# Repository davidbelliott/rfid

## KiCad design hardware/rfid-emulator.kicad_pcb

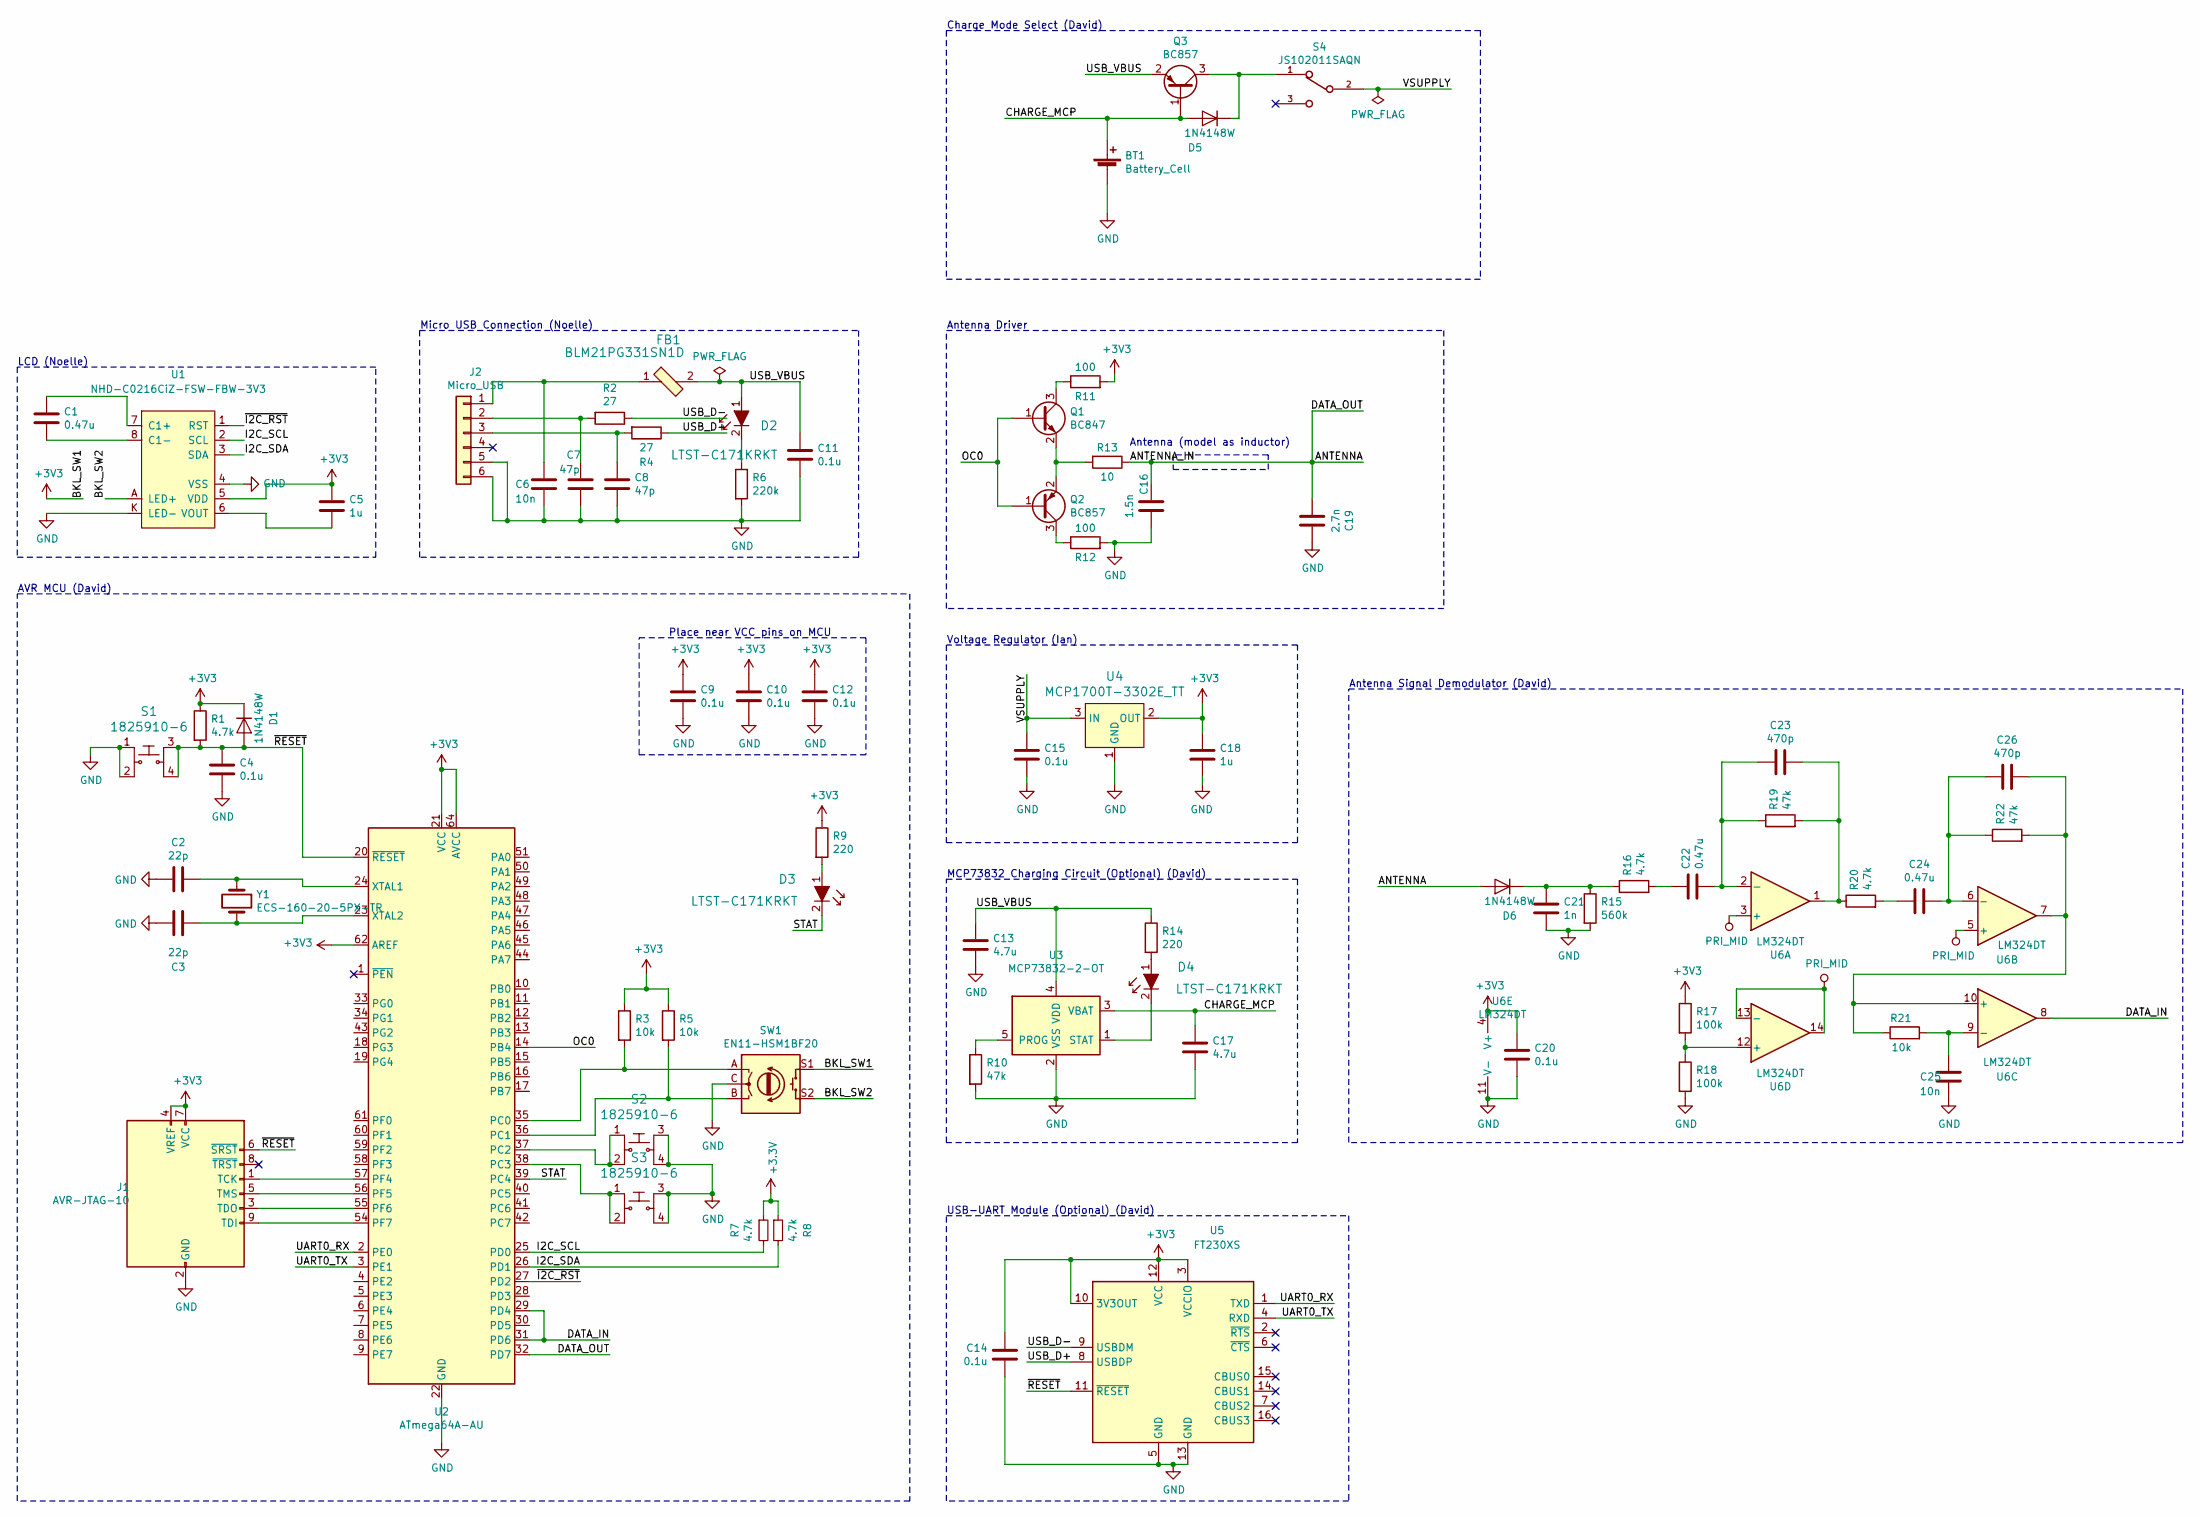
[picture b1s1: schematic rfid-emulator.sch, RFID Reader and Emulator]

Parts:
BT1: Battery_Cell; KEYSTONE-3034; Part RJD2032C1
C1: 0.47u; C_0805_HandSoldering; Part C0805C474K5RECTU
C2, C3: 22p; C_0805_HandSoldering
C4, C9, C10, C11, C12, C14, C15, C20: 0.1u; C_0805_HandSoldering; Part C0805C104Z5VACTU
C5, C18: 1u; C_0805_HandSoldering; Part CC0805ZRY5V8BB105
C6, C25: 10n; C_0805_HandSoldering; Part C0805C103K1RAC7210
C7, C8: 47p; C_0805_HandSoldering; Part C0805C470J5GACTU
C13, C17: 4.7u; C_0805_HandSoldering; Part CC0805ZRY5V6BB475
C16: 1.5n; C_0805_HandSoldering
C19: 2.7n; C_0805_HandSoldering
C21: 1n; C_0805_HandSoldering
C22, C24: 0.47u; C_0805_HandSoldering
C23, C26: 470p; C_0805_HandSoldering
D1, D5, D6: 1N4148W; D_SOD-123
D2, D3, D4: LTST-C171KRKT; 0805; MPN LTST-C171KRKT; Digi-Key_PN 160-1427-1-ND
FB1: BLM21PG331SN1D; 0805; MPN BLM21PG331SN1D; Digi-Key_PN 490-5988-1-ND
J1: AVR-JTAG-10; jtag-header; Part 302-S101
J2: Micro_USB; USB_Micro-B_Molex_47346-0001; Part Molex 47346-0001
Q1: BC847; SOT-23
Q2, Q3: BC857; SOT-23
R1, R7, R8, R16, R20: 4.7k; R_0805_HandSoldering
R2, R4: 27; R_0805_HandSoldering
R3, R5, R21: 10k; R_0805_HandSoldering
R6: 220k; R_0805_HandSoldering
R9, R14: 220; R_0805_HandSoldering
R10, R19, R22: 47k; R_0805_HandSoldering
R11, R12: 100; R_0805_HandSoldering
R13: 10; R_0805_HandSoldering
R15: 560k; R_0805_HandSoldering
R17, R18: 100k; R_0805_HandSoldering
S1, S2, S3: 1825910-6; Switch_Tactile_THT_6x6mm; MPN 1825910-6; Digi-Key_PN 450-1650-ND
S4: JS102011SAQN; SW_JS102011SAQN
SW1: EN11-HSM1BF20
U1: NHD-C0216CiZ-FSW-FBW-3V3; NHD-C0216CiZ
U2: ATmega64A-AU; TQFP-64_14x14mm_Pitch0.8mm
U3: MCP73832-2-OT; SOT-23-5_HandSoldering
U4: MCP1700T-3302E_TT; SOT-23-3; MPN MCP1700T-3302E/TT; Digi-Key_PN MCP1700T3302ETTCT-ND
U5: FT230XS; SSOP-16_3.9x4.9mm_P0.635mm
U6: LM324DT; SOIC-14_W3.9mm
Y1: ECS-160-20-5PX-TR; XTAL_ECS-160-20-5PX-TR

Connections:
/ANTENNA: C16.2, C19.2, D6.2 (A), R13.1, U2.32 (PD7)
/BKL_SW2: SW1.S2, U1.A (LED+)
/CHARGE_MCP: BT1.1 (+), C17.1, D5.2 (A), Q3.1 (B), U3.3 (VBAT)
/DATA_IN: U2.29 (PD4), U2.31 (PD6), U6.8
/I2C_SCL: R7.2, U1.2 (SCL), U2.25 (PD0)
/I2C_SDA: R8.2, U1.3 (SDA), U2.26 (PD1)
/OC0: Q1.1 (B), Q2.1 (B), U2.14 (PB4)
/STAT: D3.2, U2.39 (PC4)
/UART0_RX: U2.2 (PE0), U5.1 (TXD)
/UART0_TX: U2.3 (PE1), U5.4 (RXD)
/USB_D+: R4.1, U5.8 (USBDP)
/USB_D-: R2.1, U5.9 (USBDM)
/USB_VBUS: C11.1, C13.1, D2.1, FB1.2, Q3.2 (E), R14.1, U3.4 (VDD)
/VSUPPLY: C15.1, S4.2, U4.3 (IN)
/~I2C_RST~: U1.1 (RST), U2.27 (PD2)
/~RESET~: C4.1, D1.2 (A), J1.6 (~SRST), R1.2, S1.3, S1.4, U2.20 (~RESET), U5.11 (~RESET)
GND: BT1.2 (-), C2.2, C3.2, C4.2, C6.2, C7.2, C8.2, C9.2, C10.2, C11.2, C12.2, C13.2, C14.2, C15.2, C16.1, C17.2, C18.2, C19.1, C20.2, C21.1, C25.2, J1.2 (GND), J1.10 (GND), J2.5, J2.6, R6.2, R10.2, R12.2, R15.2, R18.2, S1.1, S1.2, S2.3, S2.4, S3.3, S3.4, SW1.C, U1.4 (VSS), U1.K (LED-), U2.22 (GND), U2.53 (GND), U2.63 (GND), U3.2 (VSS), U4.1 (GND), U5.5 (GND), U5.13 (GND), U6.11 (V-)
unnamed: C1.1, U1.7 (C1+)
unnamed: C1.2, U1.8 (C1-)
unnamed: C2.1, U2.24 (XTAL1), Y1.1
unnamed: C3.1, U2.23 (XTAL2), Y1.2
unnamed: C5.2, U1.6 (VOUT)
unnamed: C6.1, FB1.1, J2.1
unnamed: C7.1, J2.2, R2.2
unnamed: C8.1, J2.3, R4.2
unnamed: C21.2, D6.1 (K), R15.1, R16.1
unnamed: C22.1, R16.2
unnamed: C22.2, C23.2, R19.1, U6.2 (-)
unnamed: C23.1, R19.2, R20.1, U6.1
unnamed: C24.1, C26.2, R22.1, U6.6 (-)
unnamed: C24.2, R20.2
unnamed: C25.1, R21.2, U6.9 (-)
unnamed: C26.1, R21.1, R22.2, U6.7, U6.10 (+)
unnamed: D2.2, R6.1
unnamed: D3.1, R9.2
unnamed: D4.1, R14.2
unnamed: D4.2, U3.1 (STAT)
unnamed: D5.1 (K), Q3.3 (C), S4.1
unnamed: J1.1 (TCK), U2.57 (PF4)
unnamed: J1.3 (TDO), U2.55 (PF6)
unnamed: J1.5 (TMS), U2.56 (PF5)
unnamed: J1.9 (TDI), U2.54 (PF7)
unnamed: Q1.2 (E), Q2.2 (E), R13.2
unnamed: Q1.3 (C), R11.1
unnamed: Q2.3 (C), R12.1
unnamed: R3.2, SW1.A, U2.35 (PC0)
unnamed: R5.2, SW1.B, U2.36 (PC1)
unnamed: R10.1, U3.5 (PROG)
unnamed: R17.2, R18.1, U6.12 (+)
unnamed: S2.1, S2.2, U2.37 (PC2)
unnamed: S3.1, S3.2, U2.38 (PC3)
PRI_MID: U6.3 (+), U6.5 (+), U6.13 (-), U6.14

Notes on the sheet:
Place near VCC pins on MCU
USB-UART Module (Optional) (David)
Charge Mode Select (David)
Antenna Driver
Antenna Signal Demodulator (David)
AVR MCU (David)
MCP73832 Charging Circuit (Optional) (David)
Voltage Regulator (Ian)
LCD (Noelle)
Micro USB Connection (Noelle)
Antenna (model as inductor)

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
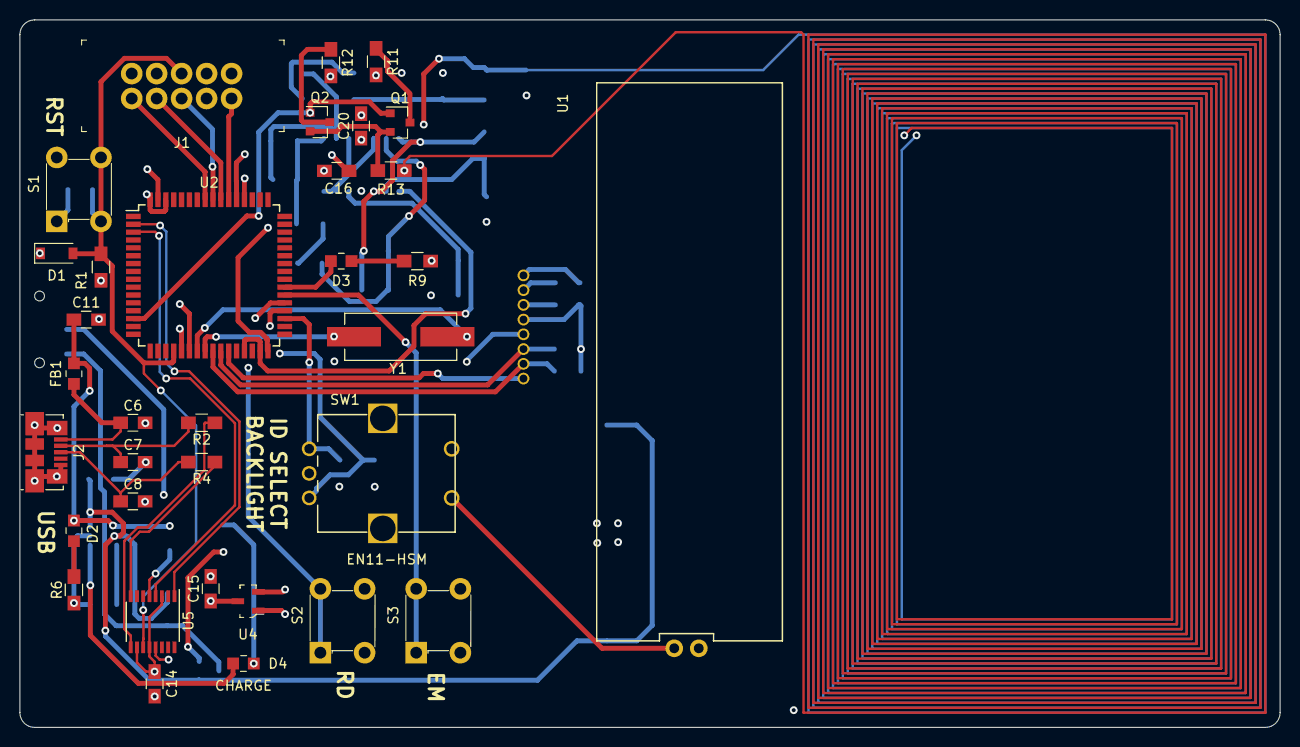
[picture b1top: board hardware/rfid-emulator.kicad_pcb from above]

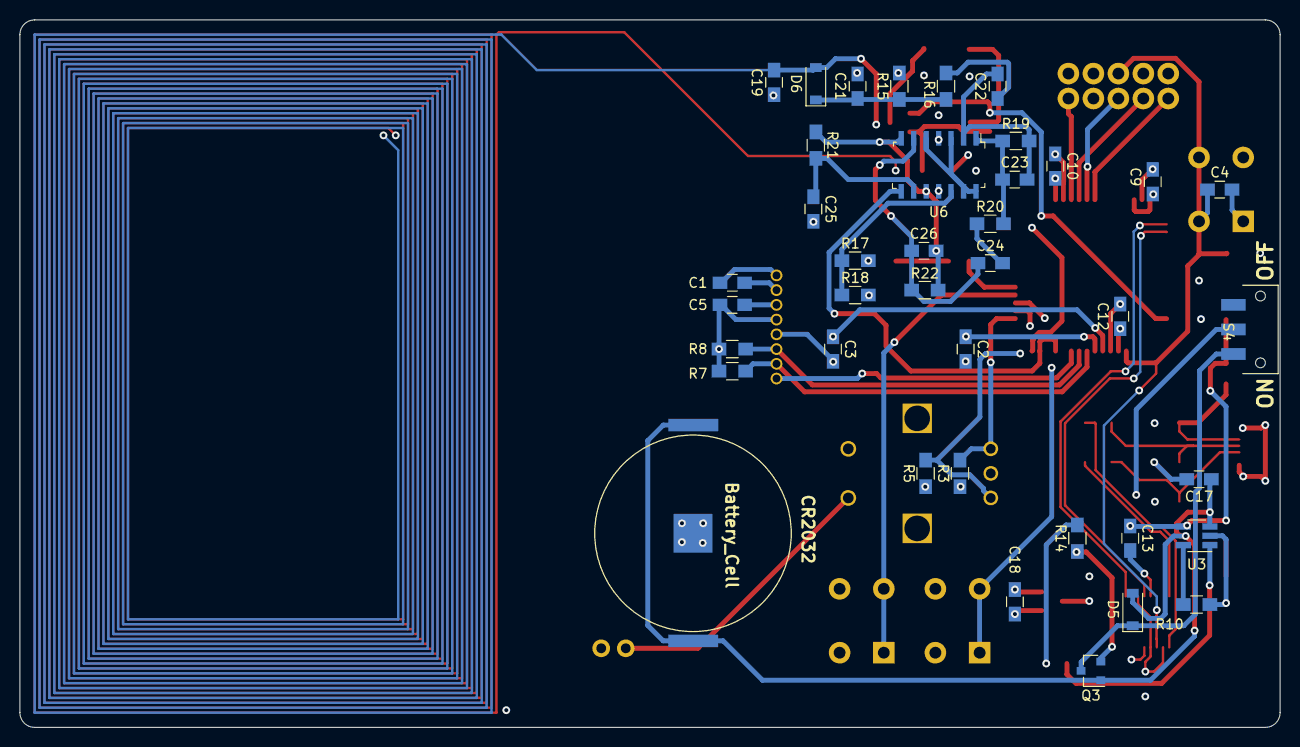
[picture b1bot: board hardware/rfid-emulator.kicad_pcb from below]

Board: 4 copper layers, 128.2 x 72.0 mm, 73 parts (39 on the bottom side), 53 nets.

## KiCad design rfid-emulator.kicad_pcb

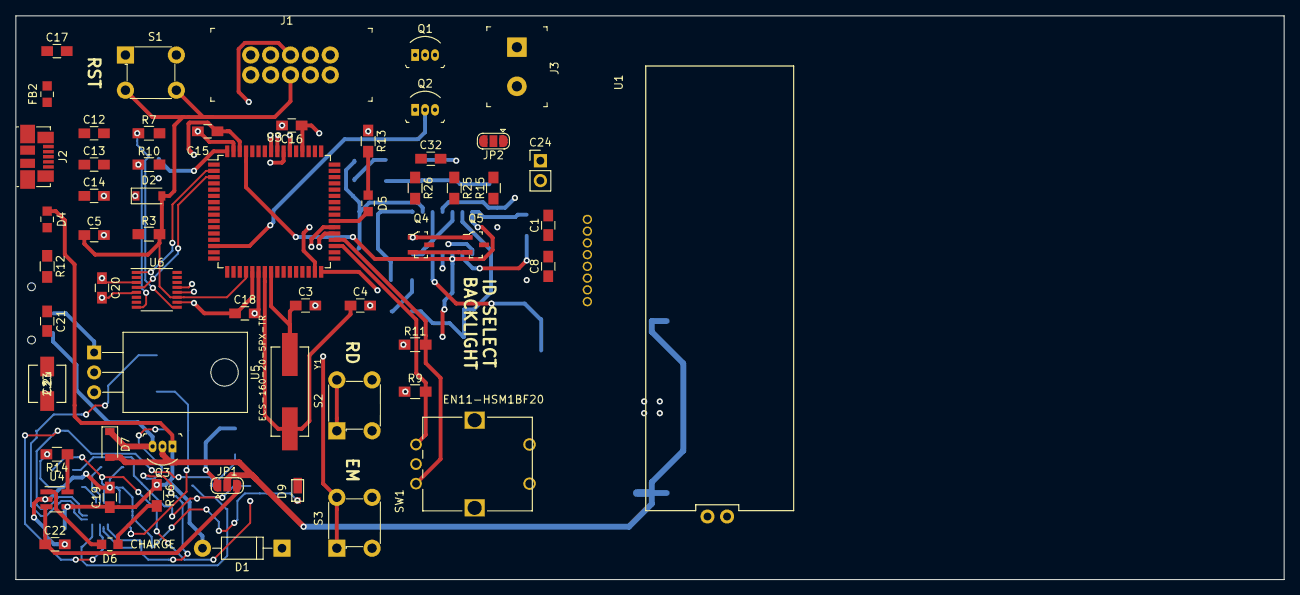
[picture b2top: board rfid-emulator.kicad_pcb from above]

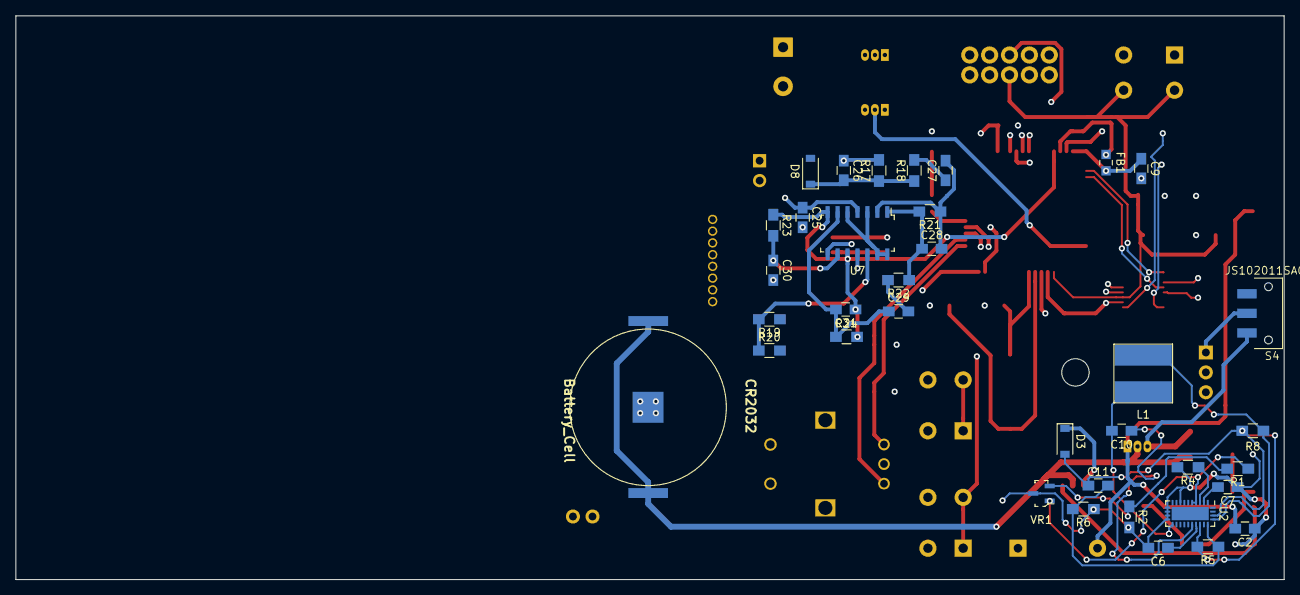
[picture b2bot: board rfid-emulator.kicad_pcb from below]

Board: 4 copper layers, 162.0 x 72.0 mm, 95 parts (36 on the bottom side), 70 nets.

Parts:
BT1: Battery_Cell; KEYSTONE-3034
C1, C27, C29: 0.47u; C_0805_HandSoldering
C2, C7, C26: 1n; C_0805_HandSoldering
C3, C4: 22p; C_0805_HandSoldering
C5, C9, C10, C15, C16, C17, C18, C20, C21, C25: 0.1u; C_0805_HandSoldering
C6, C8: 1u; C_0805_HandSoldering
C11: 10p; C_0805_HandSoldering
C12, C30: 10n; C_0805_HandSoldering
C13, C14: 47p; C_0805_HandSoldering
C19, C22: 4.7u; C_0805_HandSoldering
C23: 2.2u; EEE-1VA2R2NR
C24: 1.8n; Socket_Strip_Straight_1x02_Pitch2.54mm
C28, C31: 470p; C_0805_HandSoldering
C32: 1.5n; C_0805_HandSoldering
D1: 1N5817; D_DO-41_SOD81_P10.16mm_Horizontal
D2, D3, D7, D8: 1N4148W; D_SOD-123
D4, D5, D6: LTST-C171KRKT; 0805
D9: D_TVS; DO-219AD
FB1, FB2: BLM21PG331SN1D; 0805
J1: AVR-JTAG-10; PinHeader_2x5_P2.54mm_Drill1.2mm
J2: Micro_USB; USB_Micro-B_Molex_47346-0001
J3: OSTTC020162; Term_Block_1x2_P5mm
JP1: CHARGE_SELECT; SolderJumper-3_P1.3mm_Open_RoundedPad1.0x1.5mm
JP2: ANT_SELECT; SolderJumper-3_P1.3mm_Open_RoundedPad1.0x1.5mm
L1: 3.9u; CDRH6D28
Q1: 2N3904; TO-92-3
Q2, Q3: 2N3906; TO-92-3
Q4, Q5: IRLML6344TRPBF; SOT-23-3
R1, R2, R9, R11, R23: 10k; R_0805_HandSoldering
R3, R18, R22: 4.7k; R_0805_HandSoldering
R4: 60.4k; R_0805_HandSoldering
R5: 1M; R_0805_HandSoldering
R6: 243k; R_0805_HandSoldering
R7, R10: 27; R_0805_HandSoldering
R8: 8m; R_0805_HandSoldering
R12: 220k; R_0805_HandSoldering
R13, R16: 220; R_0805_HandSoldering
R14, R21, R24: 47k; R_0805_HandSoldering
R15: 10; R_0805_HandSoldering
R17: 560k; R_0805_HandSoldering
R19, R20: 100k; R_0805_HandSoldering
R25, R26: 100; R_0805_HandSoldering
S1, S2, S3: 1825910-6; Switch_Tactile_THT_6x6mm
S4: JS102011SAQN; SW_JS102011SAQN
SW1: EN11-HSM1BF20
U1: NHD-C0216CiZ-FSW-FBW-3V3; NHD-C0216CiZ
U2: LT8613; QFN-28-1EP_3x6mm_Pitch0.5mm
U3: ATmega64A-AU; TQFP-64_14x14mm_Pitch0.8mm
U4: MCP73832-2-OT; SOT-23-5_HandSoldering
U5: LF33_TO252; TO-220-3_Horizontal
U6: FT230XS; SSOP-16_3.9x4.9mm_P0.635mm
U7: LM324DT; SOIC-14_W3.9mm
VR1: TL431AIDBZR; SOT-23-3
Y1: ECS-160-20-5PX-TR; XTAL_ECS-160-20-5PX-TR

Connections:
+3V3: C8.1, C15.1, C16.1, C18.1, C20.1, C23.1, C25.1, D2.1, FB1.1, J1.4, J1.7, R3.1, R9.1, R11.1, R13.1, R19.1, SW1.S1, U1.5, U3.21, U3.52, U3.62, U5.3, U6.3, U6.10, U6.12, U7.4
/ANTENNA: C24.2, D8.2, D9.1, J3.2, Q4.3
/BKL_SW2: SW1.S2, U1.A
/CHARGE_LT: D3.1, JP1.1
/CHARGE_MCP: C22.1, JP1.3, U4.3
/DATA_IN_AN: C31.1, R23.1, R24.2, U3.61, U7.7, U7.10
/DATA_IN_DIG: U3.31, U7.8
/DATA_OUT: Q4.1, Q5.1, U3.32
/I2C_SCL: U1.2, U3.25
/I2C_SDA: U1.3, U3.26
/OC0: Q1.2, Q2.2, U3.14
/STAT: D5.2, U3.39
/UART0_RX: U3.2, U6.1
/UART0_TX: U3.3, U6.4
/USB_D+: R10.1, U6.8
/USB_D-: R7.1, U6.9
/USB_VBUS: C2.2, C17.1, C19.1, D1.2, D4.1, FB2.2, Q3.1, R16.1, U4.4
/VSUPPLY: C21.1, S4.2, U5.1
/~I2C_RST~: U1.1, U3.27
/~RESET~: C5.1, D2.2, J1.6, R3.2, S1.3, S1.4, U3.20, U6.11
GND: BT1.2, C2.1, C3.2, C4.2, C5.2, C6.2, C7.1, C9.2, C12.2, C13.2, C14.2, C15.2, C16.2, C17.2, C18.2, C19.2, C20.2, C21.2, C22.2, C23.2, C24.1, C25.2, C26.1, C30.2, C32.1, D9.2, J1.2, J1.10, J2.5, J2.6, Q5.3, R2.2, R4.2, R6.1, R12.2, R14.2, R17.2, R20.2, R26.2, S1.1, S1.2, S2.3, S2.4, S3.3, S3.4, SW1.C, U1.4, U1.K, U2.8, U2.11, U2.12, U2.13, U2.14, U3.22, U3.53, U3.63, U4.2, U5.2, U6.5, U6.13, U7.11, VR1.3
unnamed: BT1.1, D7.2, JP1.2, Q3.2
unnamed: C1.1, U1.7
unnamed: C1.2, U1.8
unnamed: C3.1, U3.24, Y1.1
unnamed: C4.1, U3.23, Y1.2
unnamed: C6.1, U2.21
unnamed: C7.2, U2.2
unnamed: C8.2, U1.6
unnamed: C9.1, FB1.2, U3.64
unnamed: C10.1, U2.20
unnamed: C10.2, L1.2, U2.15
unnamed: C11.1, D3.2, R5.2, R8.1, U2.22, U2.26
unnamed: C11.2, R5.1, R6.2, U2.24
unnamed: C12.1, FB2.1, J2.1
unnamed: C13.1, J2.2, R7.2
unnamed: C14.1, J2.3, R10.2
unnamed: C26.2, D8.1, R17.1, R18.1
unnamed: C27.1, R18.2
unnamed: C27.2, C28.2, R21.1, U7.2
unnamed: C28.1, R21.2, R22.1, U7.1
unnamed: C29.1, C31.2, R24.1, U7.6
unnamed: C29.2, R22.2
unnamed: C30.1, R23.2, U7.9
unnamed: C32.2, JP2.2, R15.1
unnamed: D1.1, R1.1, U2.4, U2.5, VR1.1
unnamed: D4.2, R12.1
unnamed: D5.1, R13.2
unnamed: D6.1, R16.2
unnamed: D6.2, U4.1
unnamed: D7.1, Q3.3, S4.1
unnamed: J1.1, U3.57
unnamed: J1.3, U3.55
unnamed: J1.5, U3.56
unnamed: J1.9, U3.54
unnamed: J3.1, JP2.3
unnamed: L1.1, R8.2, U2.25
unnamed: Q1.1, Q2.1, R15.2
unnamed: Q1.3, R25.1
unnamed: Q2.3, R26.1
unnamed: Q4.2, Q5.2
unnamed: R1.2, R2.1, VR1.2
unnamed: R4.1, U2.3
unnamed: R9.2, SW1.A, U3.35
unnamed: R11.2, SW1.B, U3.36
unnamed: R14.1, U4.5
unnamed: R19.2, R20.1, U7.12
unnamed: S2.1, S2.2, U3.37
unnamed: S3.1, S3.2, U3.38
PRI_MID: U7.3, U7.5, U7.13, U7.14

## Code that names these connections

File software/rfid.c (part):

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
// Pin OC0 must be configured as output before calling
void read_start(void) {
    DDRD &= ~(1 << 4);   // Configure PD4 as input (ICP1)
    DDRD &= ~(1 << 6);   // Configure PD6 as input (digital data in)
    DDRD &= ~(1 << 7);      // DATA_OUT hi-Z
    PORTD &= ~(1 << 6);
    PORTD &= ~(1 << 7);
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}

void emu_start(unsigned long long val) {
    DDRD |= (1 << 7);   // Configure PD7 as output (DATA_OUT)
    for (int i = 0; i < EMU_SEQ_SIZE; i++) {
        cur_emu_encoded[i] = i % 2;
    }
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
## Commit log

2019-10-31 Move kicad files to hardware directory
2019-11-12 Update schematic with latest changes
2019-11-17 Update schematic to fix voltage supply, reflect prototyping changes
2019-11-18 Add footprints for some components missing them
2019-11-18 Add footprints for pretty much everything
2019-11-18 Layout for most parts
2019-11-18 Re-add Noelle's changes
2019-11-18 Ian changes rfid-emulator.kicad_pcb
    Added all traces and connections associated with the battery management system.
2019-11-19 Finished driver and added antenna
2019-11-19 Fix most DRC failures on PCB check
2019-11-22 Add test points and extra capacitor socket
2019-11-23 Add aux origin and fix unrounded corner on PCB
2019-11-23 Added silkscreen beaver
2019-11-23 Fixed name typo
2019-11-30 Write preliminary firmware for read functionality
2019-12-01 Fix incorrect polarity and sample synchronization
2019-12-05 Split code up into multiple files
2019-12-09 added lcd i2c driver
2019-12-12 updated lcd driver for twi
2019-12-12 Fix bit_start neglected, driver frequency, running out of RAM
2019-12-12 Add script to set fuse bits properly
2019-12-12 Add support for assembly source
2019-12-12 LCD working
2019-12-12 Placeholder for slots; make LCD use internal booster
2019-12-13 Add TWI driver code
2019-12-13 added encoder debouncing
2019-12-13 Add button debouncing
2019-12-13 Remove debug LED toggle and fix negative wraparound for slots
2019-12-13 ensure pull-up enabled on sda
2019-12-13 Get rid of redefinition of int_to_hex_str
2019-12-13 Stop erroneously disabling debouncing interrupt
2019-12-13 Fix customer ID/version number getting cut off
2019-12-13 Implement tag mode
2019-12-13 Better align display of slot contents; get rid of slot placeholder values
2019-12-13 Use EEPROM for persistent slot data storage
2019-12-22 Remove unnecessary components and apply fixes from V0.1

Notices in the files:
parts and their libraries:
Copyright 2016 Accelerated Designs. All rights reserved.
